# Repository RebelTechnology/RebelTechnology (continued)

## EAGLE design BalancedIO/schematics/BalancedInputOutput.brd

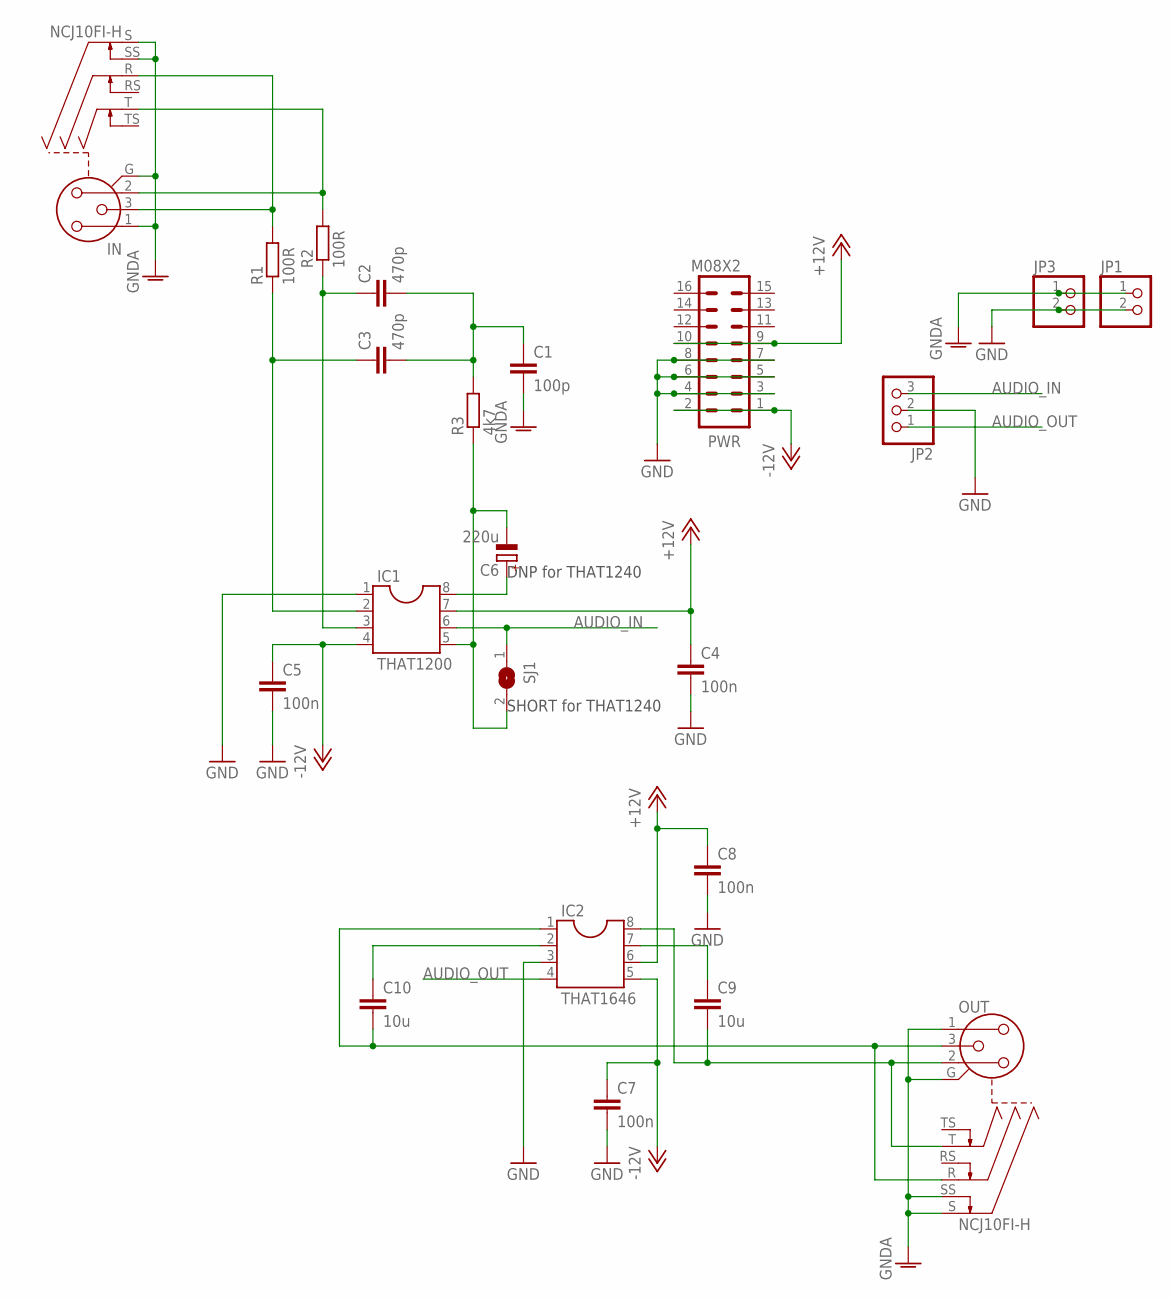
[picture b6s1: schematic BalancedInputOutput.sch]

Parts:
C1: 100p; C050-025X075
C2, C3: 470p; C050-025X075
C4, C5, C7, C8: 100n; C050-025X075
C6: 220u; E5-8,5
C9, C10: 10u; C050-025X075
IC1: THAT1200; DIL08
IC2: THAT1646; DIL08
IN: NCJ10FI-H
JP1, JP3: PINHD-1X2; 1X02
JP2: PINHD-1X3; 1X03
OUT: NCJ10FI-H
PWR: M08X2; 2X8
R1, R2: 100R; 0207/7
R3: 4k7; 0207/7
SJ1: SJW

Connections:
+12V: C4.1, C8.1, IC1.7, IC2.6, PWR.9, PWR.10
-12V: C5.1, C7.1, IC1.4, IC2.5, PWR.1, PWR.2
AUDIO_IN: IC1.6, JP2.3, SJ1.1
AUDIO_OUT: IC2.4, JP2.1
GND: C4.2, C5.2, C7.2, C8.2, IC1.1, IC2.3, JP1.2, JP2.2, JP3.2, PWR.3, PWR.4, PWR.5, PWR.6, PWR.7, PWR.8
GNDA: C1.2, IN.1, IN.G, IN.S, IN.SS, JP1.1, JP3.1, OUT.1, OUT.G, OUT.S, OUT.SS
unnamed: C3.1, IC1.2, R1.1
unnamed: IN.3, IN.R, R1.2
unnamed: C2.1, IC1.3, R2.1
unnamed: IN.2, IN.T, R2.2
unnamed: C6.-, IC1.5, R3.1, SJ1.2
unnamed: C1.1, C2.2, C3.2, R3.2
unnamed: C9.1, IC2.7
unnamed: C10.1, IC2.2
unnamed: C6.+, IC1.8
unnamed: C9.2, IC2.8, OUT.2, OUT.T
unnamed: C10.2, IC2.1, OUT.3, OUT.R

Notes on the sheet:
DNP for THAT1240
SHORT for THAT1240

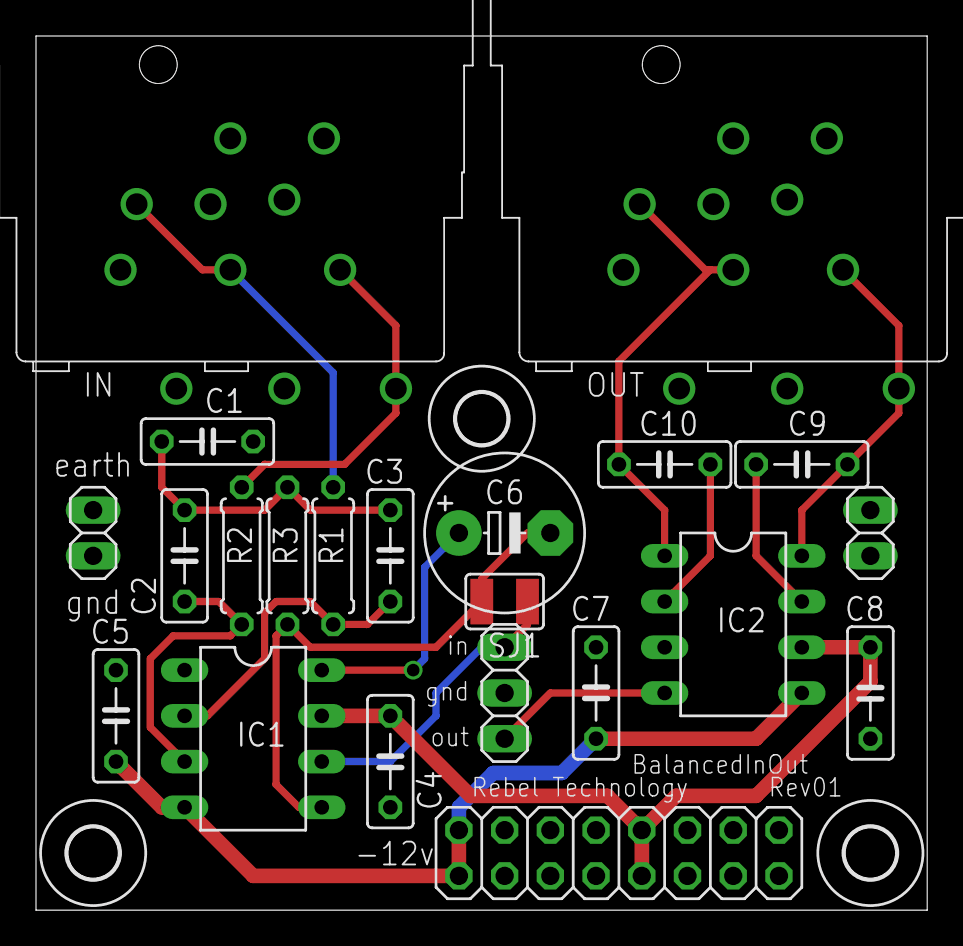
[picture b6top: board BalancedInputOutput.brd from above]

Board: 2 copper layers, 49.5 x 48.6 mm, 25 parts (0 on the bottom side), 17 nets.

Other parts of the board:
U$1, U$2, U$3: 2,8

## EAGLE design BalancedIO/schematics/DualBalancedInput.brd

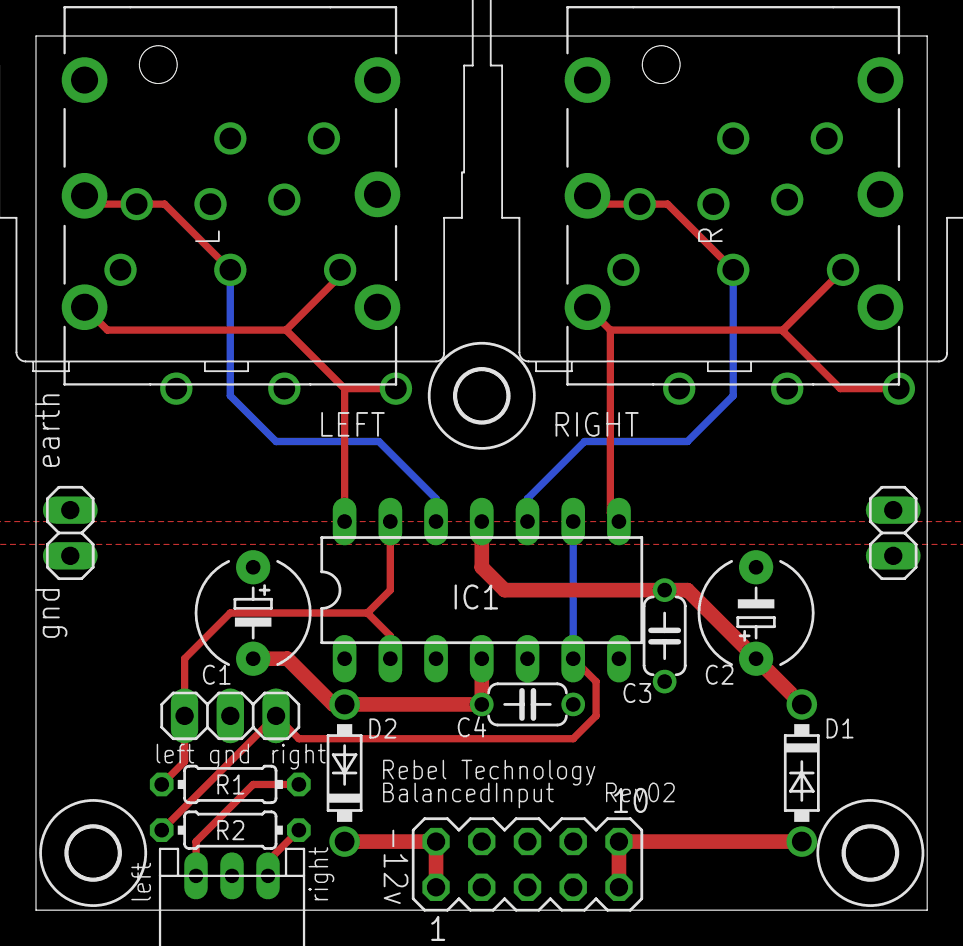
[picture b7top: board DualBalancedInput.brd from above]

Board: 2 copper layers, 49.5 x 48.6 mm, 21 parts (0 on the bottom side), 14 nets.

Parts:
C1, C2: 10u; E5-6
C3, C4: 100n; C050-024X044
D1, D2: 1N5817; DO41-7.6
IC1: INA2137P; DIL14
J1: CON-JST_PH_3W
JP1, JP3: 1X02
JP2: 1X03
L: NEUTRIK_NMJ6HCD2; NMJ6HCD2
LEFT: NCJ10FI-H
R: NEUTRIK_NMJ6HCD2; NMJ6HCD2
R1, R2: 100R; 0204/7
RIGHT: NCJ10FI-H
SV1: MA05-2
U$1, U$2, U$3: 2,8

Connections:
+12V: C2.+, C3.1, D1.C, IC1.11
-12V: C1.-, C4.1, D2.A, IC1.4
GND: C1.+, C2.-, C3.2, C4.2, IC1.3, IC1.5, J1.P2, JP1.2, JP2.2, JP3.2, SV1.3, SV1.4, SV1.5, SV1.6, SV1.7, SV1.8
GNDA: JP1.1, JP3.1, L.S, L.SN, LEFT.1, LEFT.G, LEFT.S, LEFT.SS, R.S, R.SN, RIGHT.1, RIGHT.G, RIGHT.S, RIGHT.SS
IN_LEFT: IC1.2, IC1.13, JP2.3, R1.1
IN_RIGHT: IC1.6, IC1.9, JP2.1, R2.1
unnamed: IC1.14, L.T, LEFT.2, LEFT.T
unnamed: IC1.12, L.R, LEFT.3, LEFT.R
unnamed: D2.C, SV1.1, SV1.2
unnamed: D1.A, SV1.9, SV1.10
unnamed: J1.P3, R2.2
unnamed: J1.P1, R1.2
unnamed: IC1.8, R.T, RIGHT.2, RIGHT.T
unnamed: IC1.10, R.R, RIGHT.3, RIGHT.R
